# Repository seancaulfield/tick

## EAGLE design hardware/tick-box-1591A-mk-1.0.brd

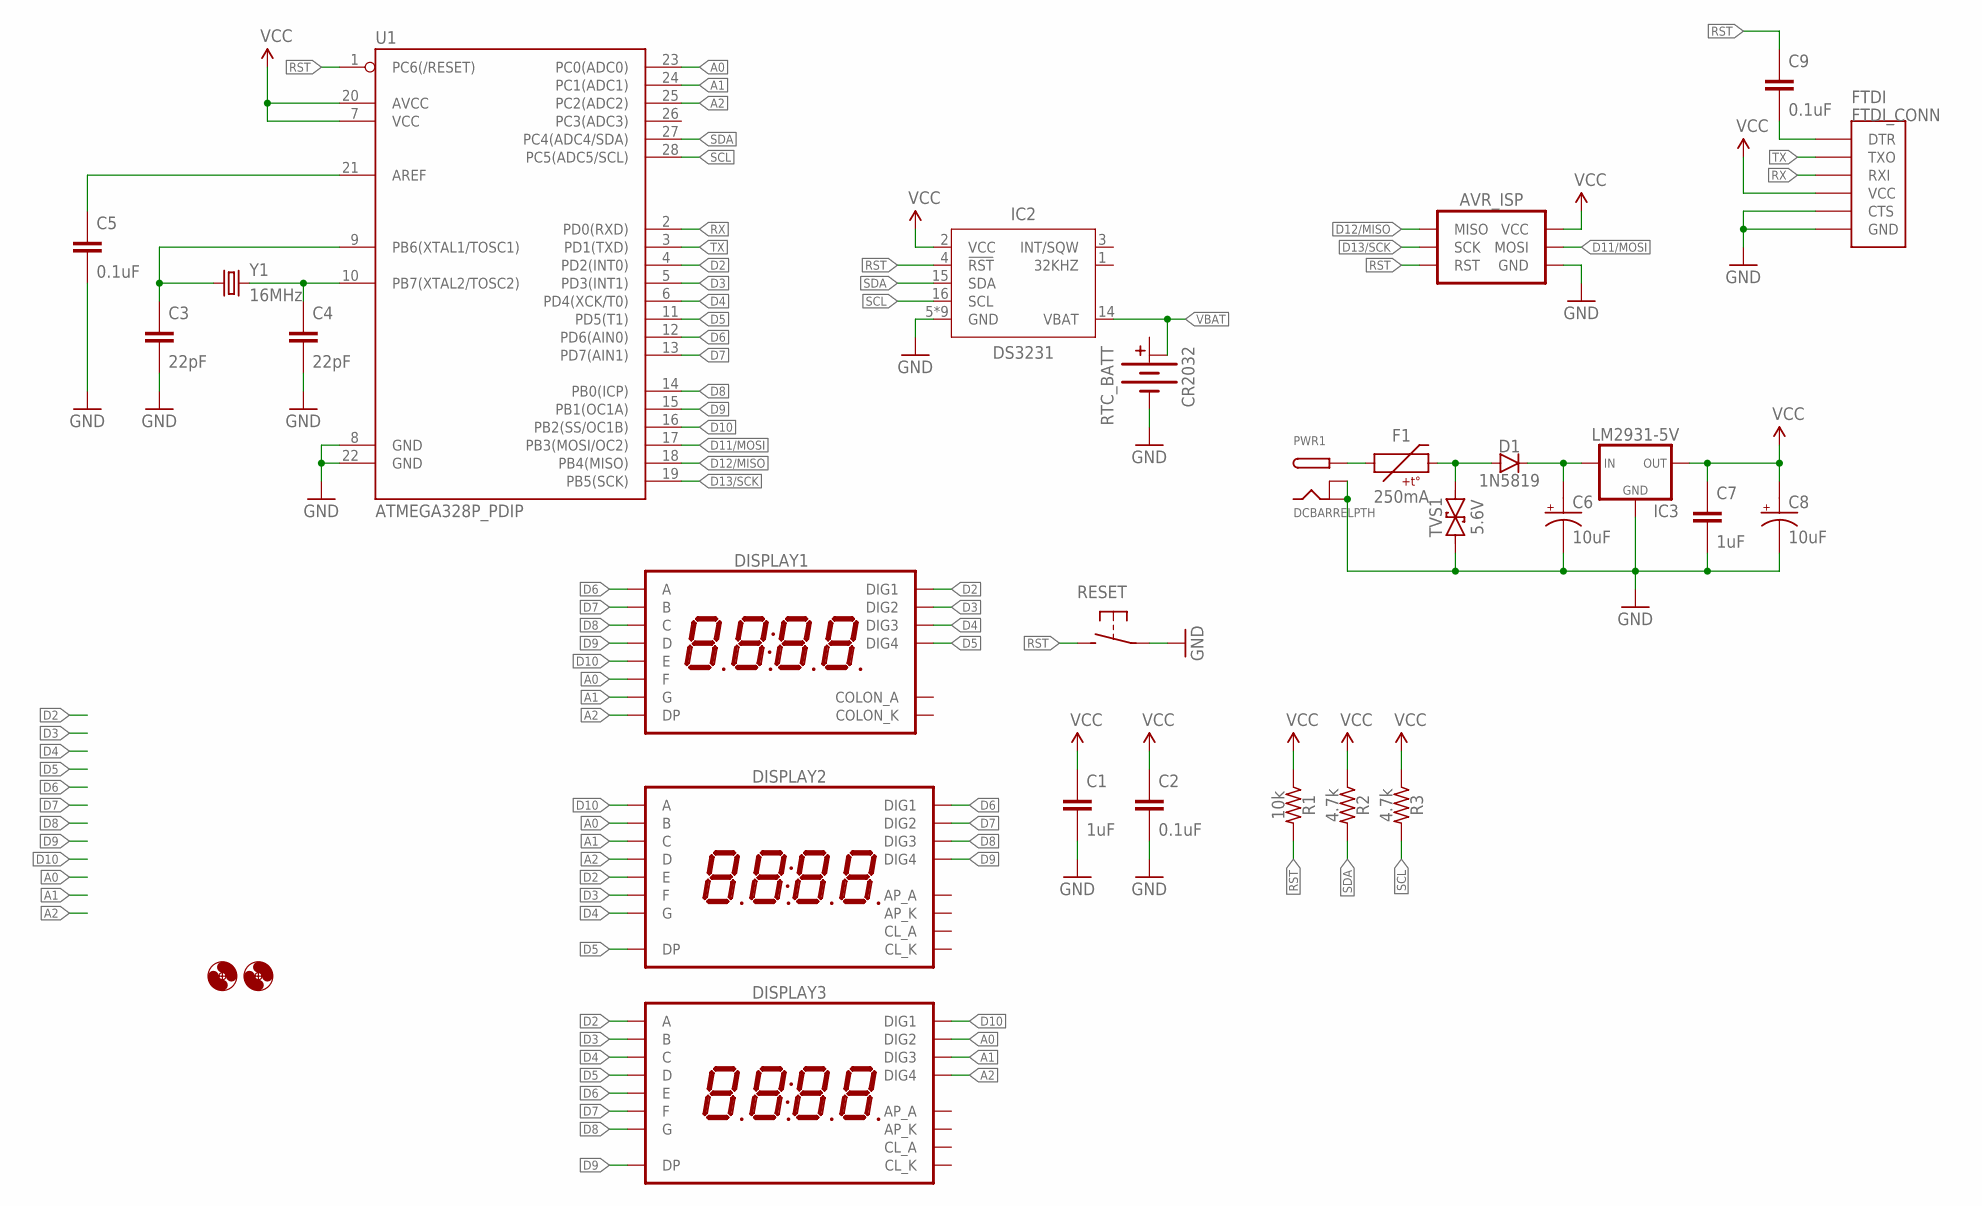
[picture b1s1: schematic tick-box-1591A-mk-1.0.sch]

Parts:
AVR_ISP: AVR_SPI_PRG_6PTH; 2X3
C1, C7: 1uF; C025-024X044
C2, C5, C9: 0.1uF; C025-024X044
C3, C4: 22pF; C025-024X044
C6, C8: 10uF; E2-5
D1: 1N5819; DIODE-10.16MM
DISPLAY1: 7SEG_4DIGIT_COLON14.2MM-CC-NS; 7SEG_4DIG_NS
DISPLAY2, DISPLAY3: 7SEG_4DIGIT_COLON_APOS; 7SEG_4DIG_10MM
F1: 250mA; PTC-PTH-5.08MM
FTDI: FTDI_CONN
H1, H2: HOLE#2; HOLE-#2
IC2: DS3231; SO16W
IC3: LM2931-5V; TO-92-AMMO
PWR1: DCBARRELPTH; DCJACK_2MM_PTH
R1: 10k; RESISTOR-AXIAL-PTH-7.62MM
R2, R3: 4.7k; RESISTOR-AXIAL-PTH-7.62MM
RESET: SPST-NO-TACT6MM-PTH-SMALL-PADS; DTS-6-SMALL-PADS
RTC_BATT: CR2032; BATTCON_20MM_MINE
TVS1: 5.6V; DO-41-TVS
U1: ATMEGA328P_PDIP; DIL28-3
Y1: 16MHz; HC49U-V

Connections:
A0: DISPLAY1.P$12 (F), DISPLAY2.16 (B), DISPLAY3.2 (DIG2), U1.23 (PC0(ADC0))
A1: DISPLAY1.P$5 (G), DISPLAY2.13 (C), DISPLAY3.6 (DIG3), U1.24 (PC1(ADC1))
A2: DISPLAY1.P$3 (DP), DISPLAY2.3 (D), DISPLAY3.8 (DIG4), U1.25 (PC2(ADC2))
D2: DISPLAY1.P$14 (DIG1), DISPLAY2.5 (E), DISPLAY3.14 (A), U1.4 (PD2(INT0))
D3: DISPLAY1.P$11 (DIG2), DISPLAY2.11 (F), DISPLAY3.16 (B), U1.5 (PD3(INT1))
D4: DISPLAY1.P$10 (DIG3), DISPLAY2.15 (G), DISPLAY3.13 (C), U1.6 (PD4(XCK/T0))
D5: DISPLAY1.P$6 (DIG4), DISPLAY2.7 (DP), DISPLAY3.3 (D), U1.11 (PD5(T1))
D6: DISPLAY1.P$13 (A), DISPLAY2.1 (DIG1), DISPLAY3.5 (E), U1.12 (PD6(AIN0))
D7: DISPLAY1.P$9 (B), DISPLAY2.2 (DIG2), DISPLAY3.11 (F), U1.13 (PD7(AIN1))
D8: DISPLAY1.P$4 (C), DISPLAY2.6 (DIG3), DISPLAY3.15 (G), U1.14 (PB0(ICP))
D9: DISPLAY1.P$2 (D), DISPLAY2.8 (DIG4), DISPLAY3.7 (DP), U1.15 (PB1(OC1A))
D10: DISPLAY1.P$1 (E), DISPLAY2.14 (A), DISPLAY3.1 (DIG1), U1.16 (PB2(SS/OC1B))
D11/MOSI: AVR_ISP.4 (MOSI), U1.17 (PB3(MOSI/OC2))
D12/MISO: AVR_ISP.1 (MISO), U1.18 (PB4(MISO))
D13/SCK: AVR_ISP.3 (SCK), U1.19 (PB5(SCK))
GND: AVR_ISP.6 (GND), C1.2, C2.2, C3.2, C4.2, C5.2, C6.-, C7.2, C8.-, FTDI.CTS, FTDI.GND, IC2.5 (GND), IC2.6 (GND), IC2.7 (GND), IC2.8 (GND), IC2.9 (GND), IC2.10 (GND), IC2.11 (GND), IC2.12 (GND), IC2.13 (GND), IC3.2 (GND), PWR1.BRK, PWR1.GND, RESET.1, RESET.2 (1), RTC_BATT.BOTTOM (-), TVS1.P$1 (1), U1.8 (GND), U1.22 (GND)
unnamed: C4.1, U1.10 (PB7(XTAL2/TOSC2)), Y1.2
unnamed: C3.1, U1.9 (PB6(XTAL1/TOSC1)), Y1.1
unnamed: C6.+, D1.C, IC3.1 (IN)
unnamed: F1.P$1 (1), PWR1.PWR
unnamed: C5.1, U1.21 (AREF)
unnamed: D1.A, F1.P$2 (2), TVS1.P$2 (2)
unnamed: C9.2, FTDI.DTR
RST: AVR_ISP.5 (RST), C9.1, IC2.4 (!RST), R1.P$2 (2), RESET.3 (2), RESET.4 (2), U1.1 (PC6(/RESET))
RX: FTDI.RXI, U1.2 (PD0(RXD))
SCL: IC2.16 (SCL), R3.P$2 (2), U1.28 (PC5(ADC5/SCL))
SDA: IC2.15 (SDA), R2.P$2 (2), U1.27 (PC4(ADC4/SDA))
TX: FTDI.TXO, U1.3 (PD1(TXD))
VBAT: IC2.14 (VBAT), RTC_BATT.TOP@2 (+1)
VCC: AVR_ISP.2 (VCC), C1.1, C2.1, C7.1, C8.+, FTDI.VCC, IC2.2 (VCC), IC3.3 (OUT), R1.P$1 (1), R2.P$1 (1), R3.P$1 (1), U1.7 (VCC), U1.20 (AVCC)

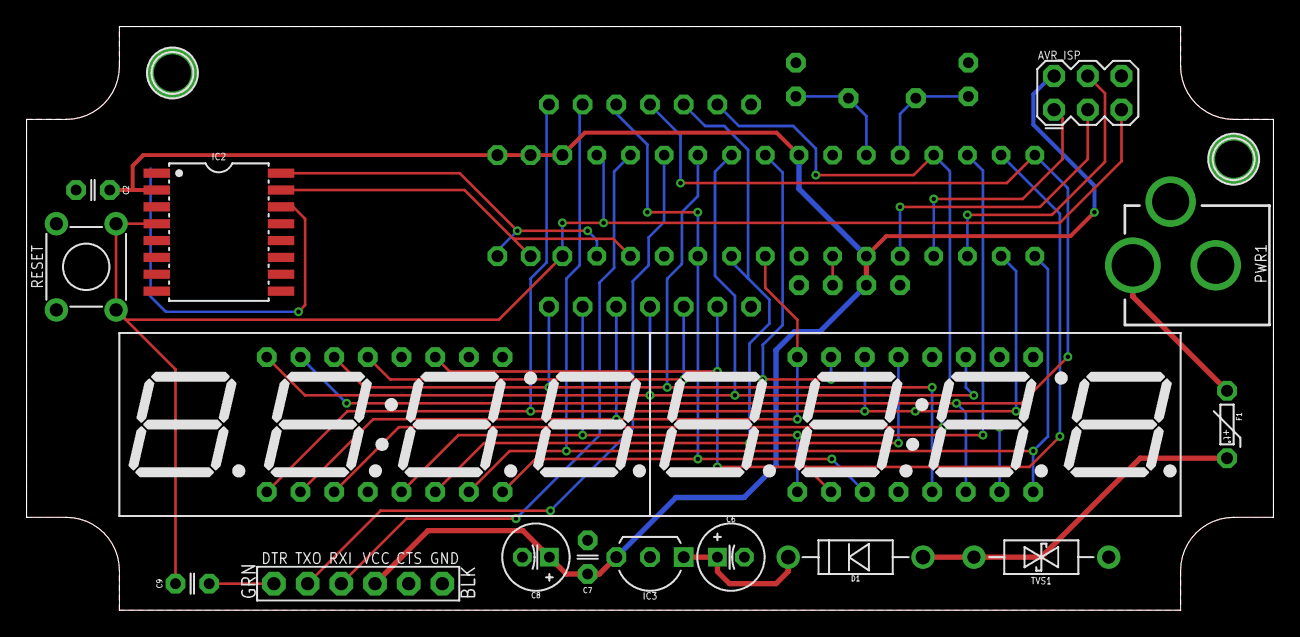
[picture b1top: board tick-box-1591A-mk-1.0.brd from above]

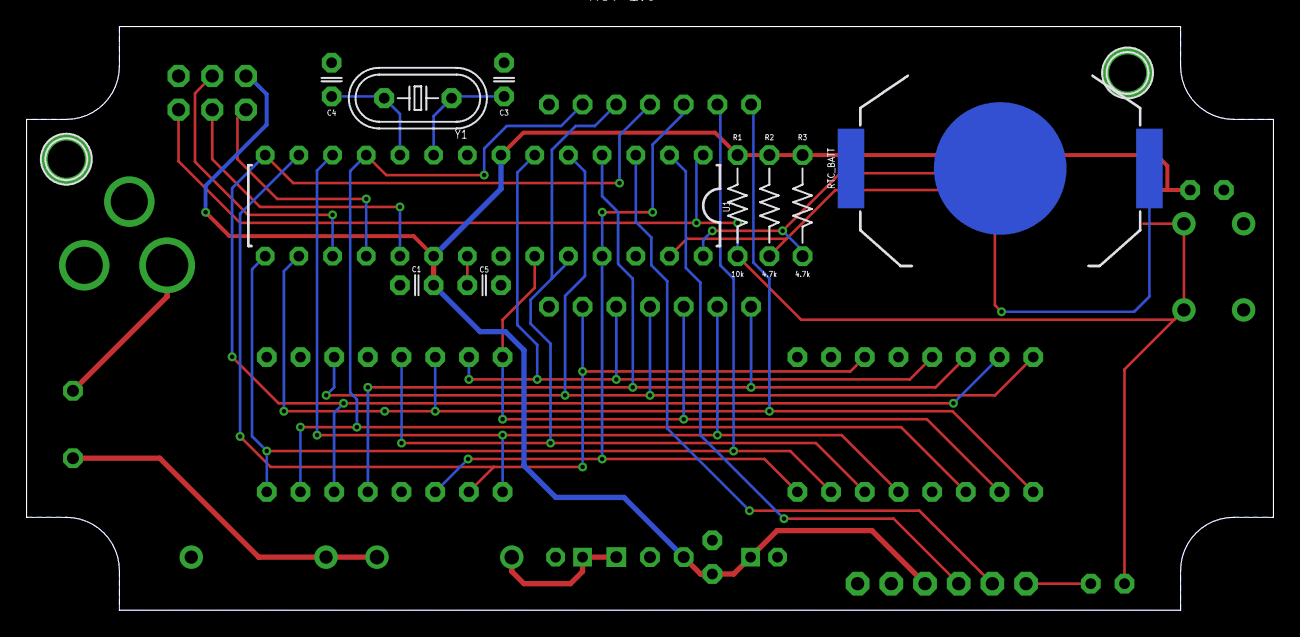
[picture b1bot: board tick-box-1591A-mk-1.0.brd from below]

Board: 2 copper layers, 94.0 x 44.0 mm, 29 parts (10 on the bottom side), 30 nets.

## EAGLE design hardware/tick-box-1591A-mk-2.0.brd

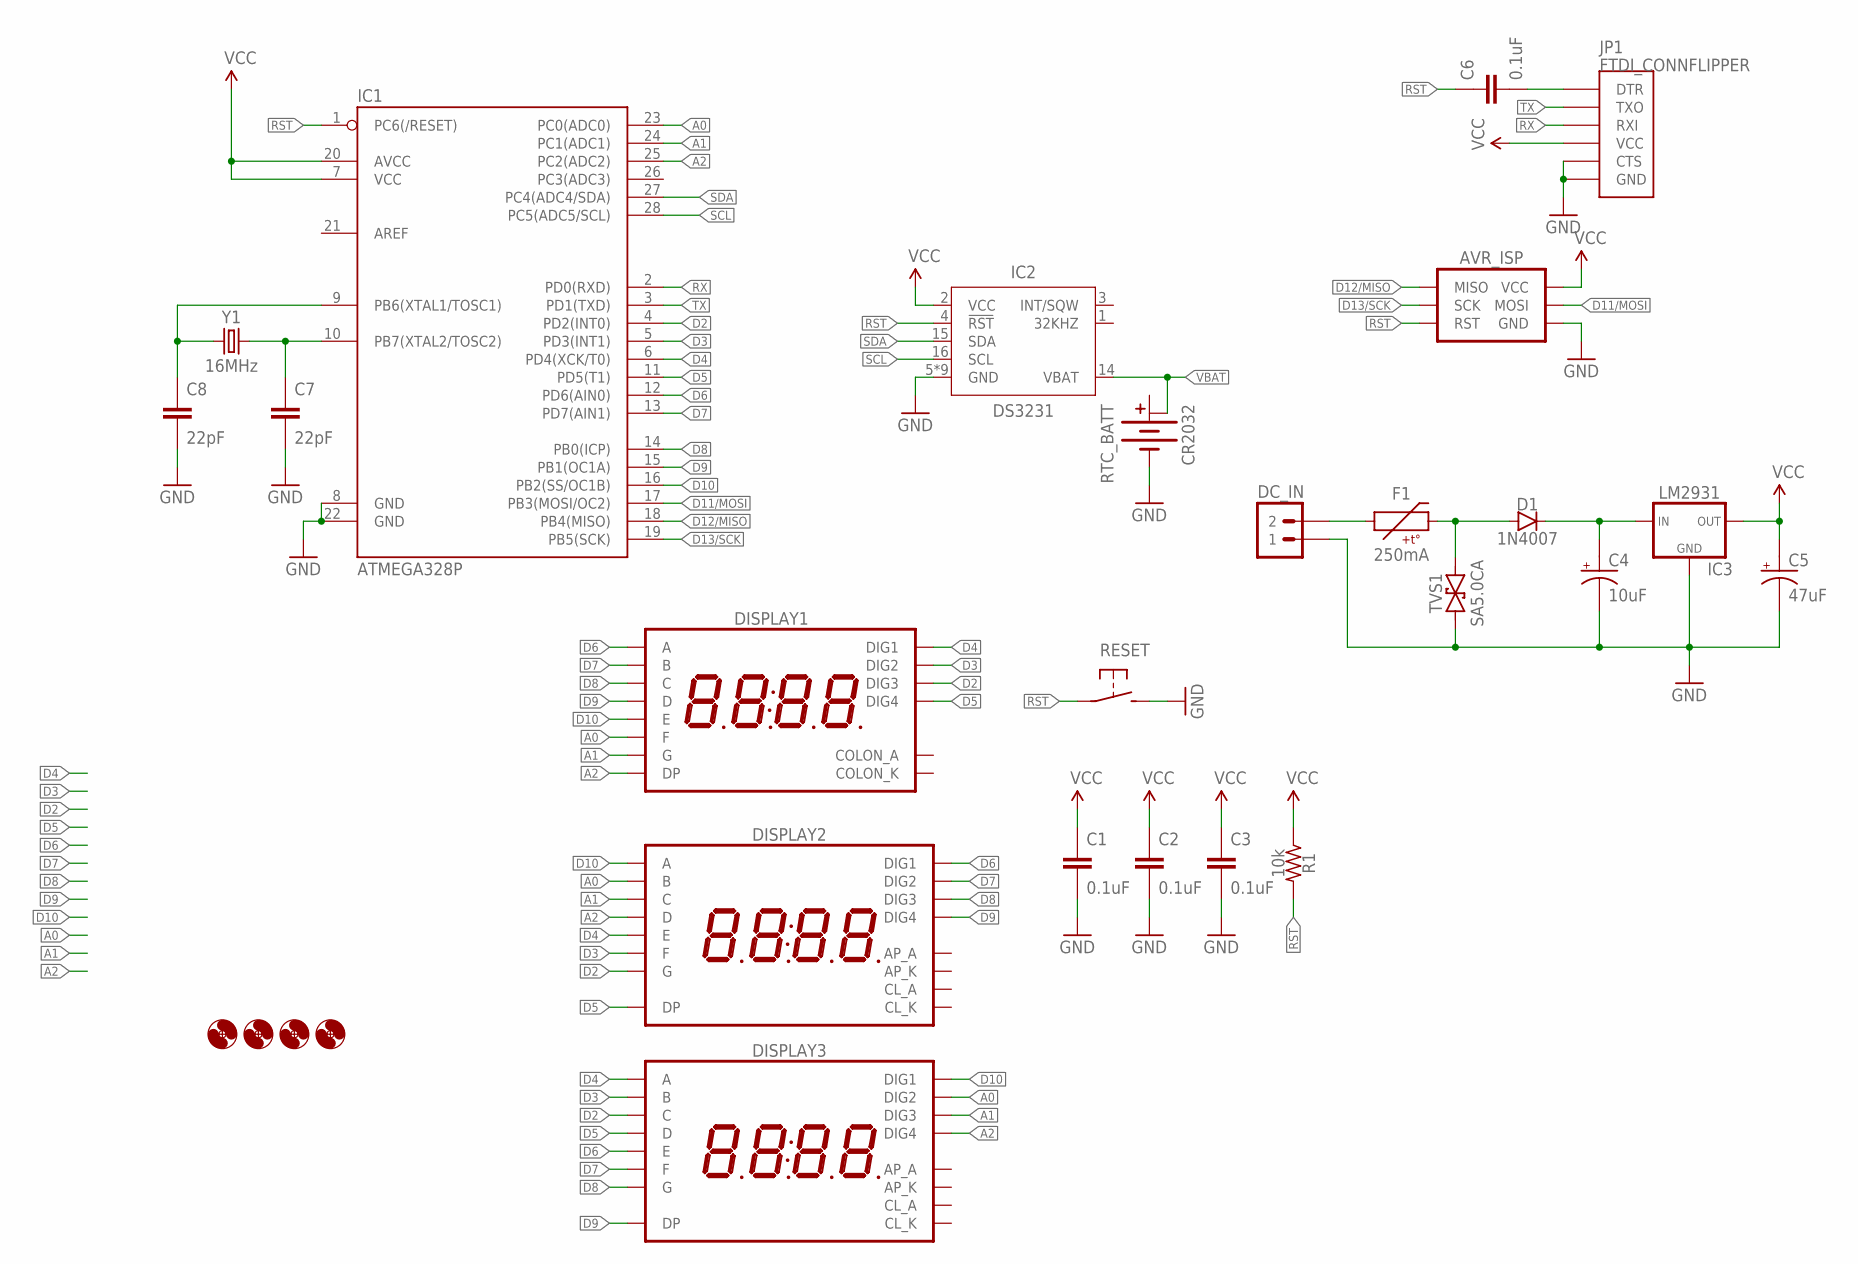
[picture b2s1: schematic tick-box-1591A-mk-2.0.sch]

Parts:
AVR_ISP: AVR_SPI_PRG_6PTH; 2X3
C1, C2, C3, C6: 0.1uF; C025-024X044
C4: 10uF; E2-4
C5: 47uF; E2-4
C7, C8: 22pF; C025-024X044
D1: 1N4007; DIODE-10.16MM
DC_IN: M02PTH; 1X02
DISPLAY1: 7SEG_4DIGIT_COLON14.2MM-CC-NS; 7SEG_4DIG_NS
DISPLAY2, DISPLAY3: 7SEG_4DIGIT_COLON_APOS; 7SEG_4DIG_10MM
F1: 250mA; PTC-1206
H1, H2, H3, H4: HOLE#2; HOLE-#2
IC1: ATMEGA328P; DIL28-3
IC2: DS3231; SO16W
IC3: LM2931; TO-92-AMMO
JP1: FTDI_CONNFLIPPER; FTDI_CONN_FLIP
R1: 10k; RESISTOR-AXIAL-PTH-6.35MM
RESET: SPST-NO-TACT3MM-PTH-SMALL-PADS; DTS-3-SMALL-PADS
RTC_BATT: CR2032; BATTCON_20MM_MINE
TVS1: SA5.0CA; DO-41-TVS-BI-10.16MM
Y1: 16MHz; HC49U-V

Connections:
A0: DISPLAY1.P$12 (F), DISPLAY2.16 (B), DISPLAY3.2 (DIG2), IC1.23 (PC0(ADC0))
A1: DISPLAY1.P$5 (G), DISPLAY2.13 (C), DISPLAY3.6 (DIG3), IC1.24 (PC1(ADC1))
A2: DISPLAY1.P$3 (DP), DISPLAY2.3 (D), DISPLAY3.8 (DIG4), IC1.25 (PC2(ADC2))
D2: DISPLAY1.P$10 (DIG3), DISPLAY2.15 (G), DISPLAY3.13 (C), IC1.4 (PD2(INT0))
D3: DISPLAY1.P$11 (DIG2), DISPLAY2.11 (F), DISPLAY3.16 (B), IC1.5 (PD3(INT1))
D4: DISPLAY1.P$14 (DIG1), DISPLAY2.5 (E), DISPLAY3.14 (A), IC1.6 (PD4(XCK/T0))
D5: DISPLAY1.P$6 (DIG4), DISPLAY2.7 (DP), DISPLAY3.3 (D), IC1.11 (PD5(T1))
D6: DISPLAY1.P$13 (A), DISPLAY2.1 (DIG1), DISPLAY3.5 (E), IC1.12 (PD6(AIN0))
D7: DISPLAY1.P$9 (B), DISPLAY2.2 (DIG2), DISPLAY3.11 (F), IC1.13 (PD7(AIN1))
D8: DISPLAY1.P$4 (C), DISPLAY2.6 (DIG3), DISPLAY3.15 (G), IC1.14 (PB0(ICP))
D9: DISPLAY1.P$2 (D), DISPLAY2.8 (DIG4), DISPLAY3.7 (DP), IC1.15 (PB1(OC1A))
D10: DISPLAY1.P$1 (E), DISPLAY2.14 (A), DISPLAY3.1 (DIG1), IC1.16 (PB2(SS/OC1B))
D11/MOSI: AVR_ISP.4 (MOSI), IC1.17 (PB3(MOSI/OC2))
D12/MISO: AVR_ISP.1 (MISO), IC1.18 (PB4(MISO))
D13/SCK: AVR_ISP.3 (SCK), IC1.19 (PB5(SCK))
GND: AVR_ISP.6 (GND), C1.2, C2.2, C3.2, C4.-, C5.-, C7.2, C8.2, DC_IN.1, IC1.8 (GND), IC1.22 (GND), IC2.5 (GND), IC2.6 (GND), IC2.7 (GND), IC2.8 (GND), IC2.9 (GND), IC2.10 (GND), IC2.11 (GND), IC2.12 (GND), IC2.13 (GND), IC3.2 (GND), JP1.CTS, JP1.GND, RESET.2, RTC_BATT.BOTTOM (-), TVS1.P$1 (1)
unnamed: C7.1, IC1.10 (PB7(XTAL2/TOSC2)), Y1.1
unnamed: C8.1, IC1.9 (PB6(XTAL1/TOSC1)), Y1.2
unnamed: D1.A, F1.2, TVS1.P$2 (2)
unnamed: DC_IN.2, F1.1
unnamed: C4.+, D1.C, IC3.1 (IN)
unnamed: C6.2, JP1.DTR
RST: AVR_ISP.5 (RST), C6.1, IC1.1 (PC6(/RESET)), IC2.4 (!RST), R1.P$2 (2), RESET.1
RX: IC1.2 (PD0(RXD)), JP1.RXI
SCL: IC1.28 (PC5(ADC5/SCL)), IC2.16 (SCL)
SDA: IC1.27 (PC4(ADC4/SDA)), IC2.15 (SDA)
TX: IC1.3 (PD1(TXD)), JP1.TXO
VBAT: IC2.14 (VBAT), RTC_BATT.TOP@2 (+1)
VCC: AVR_ISP.2 (VCC), C1.1, C2.1, C3.1, C5.+, IC1.7 (VCC), IC1.20 (AVCC), IC2.2 (VCC), IC3.3 (OUT), JP1.VCC, R1.P$1 (1)

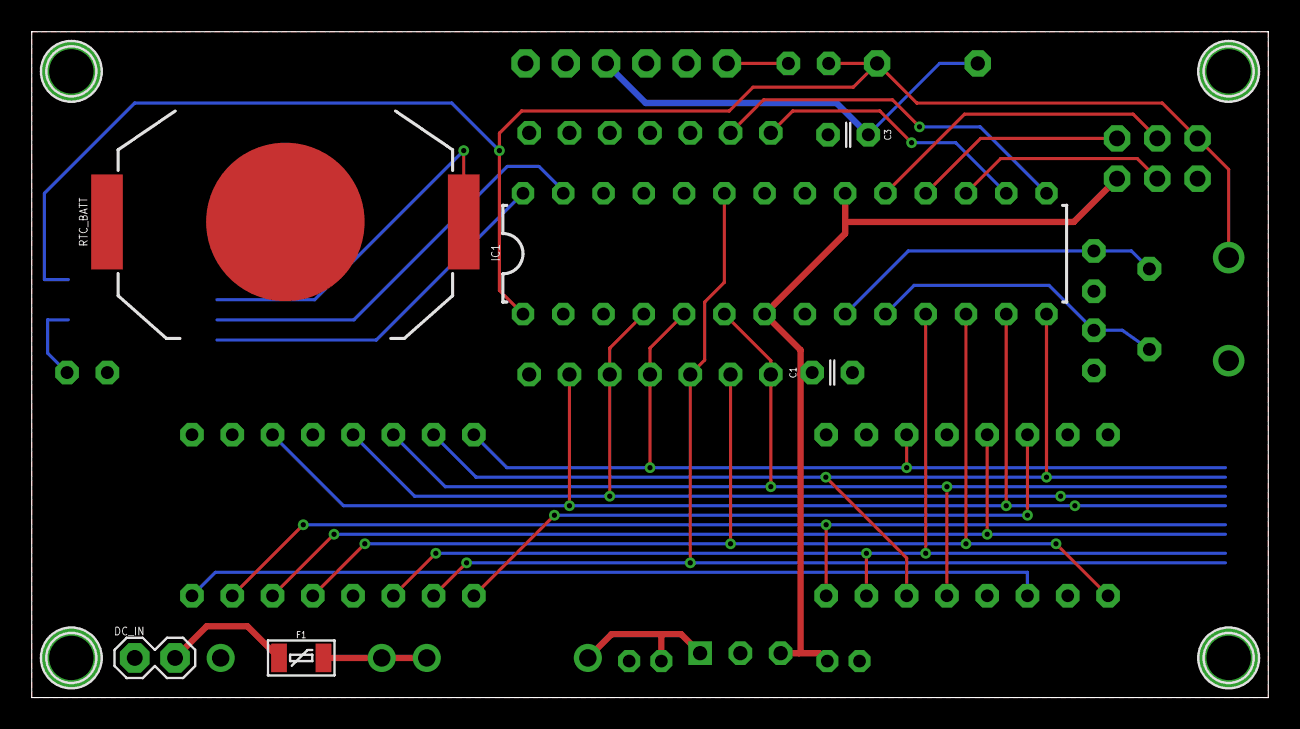
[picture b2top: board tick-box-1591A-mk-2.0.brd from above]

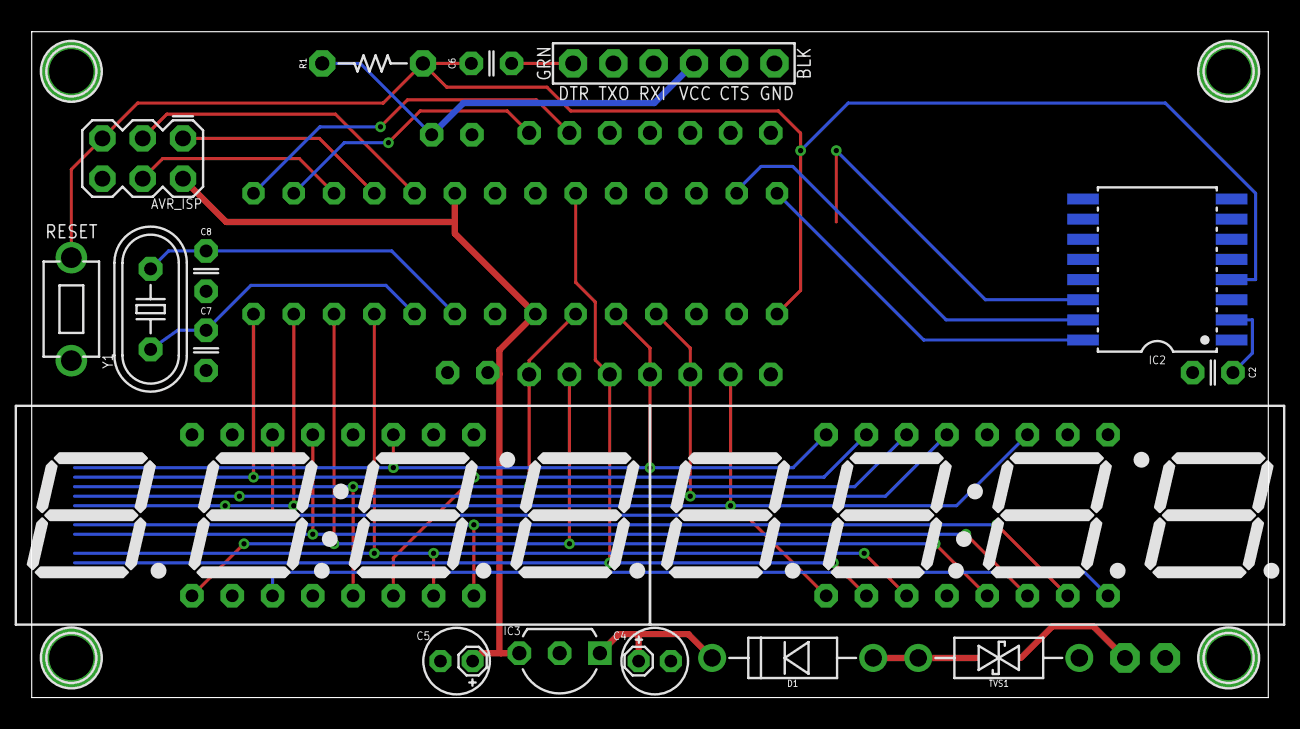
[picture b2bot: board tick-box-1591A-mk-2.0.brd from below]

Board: 2 copper layers, 78.0 x 42.0 mm, 28 parts (18 on the bottom side), 29 nets.

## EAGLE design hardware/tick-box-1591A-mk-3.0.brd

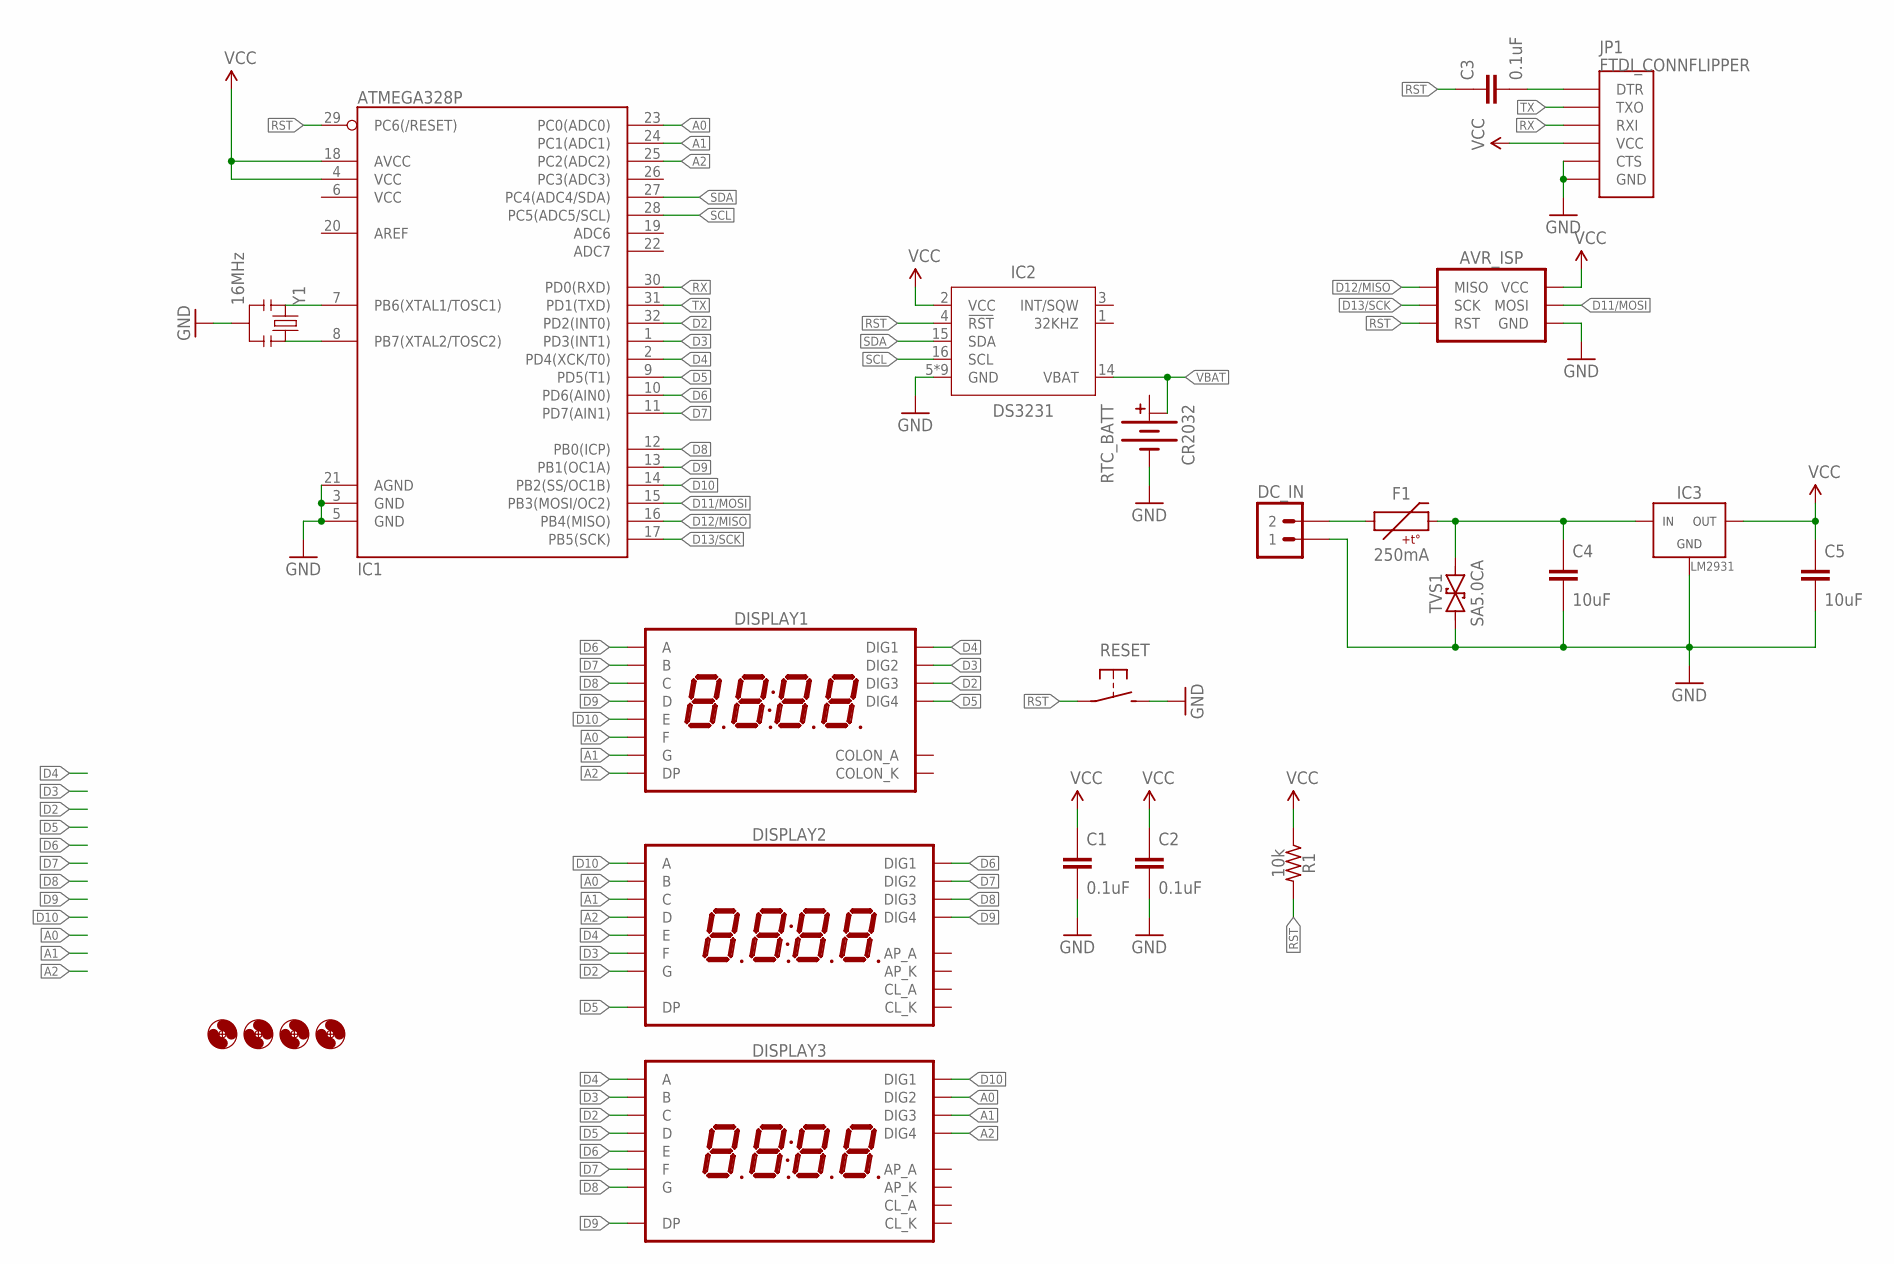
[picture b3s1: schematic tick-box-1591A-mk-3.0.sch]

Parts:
AVR_ISP: AVR_SPI_PRG_6PTH; 2X3
C1, C2, C3: 0.1uF; C0603
C4, C5: 10uF; C1206
DC_IN: M02PTH; 1X02
DISPLAY1: 7SEG_4DIGIT_COLON14.2MM-CC-NS; 7SEG_4DIG_NS
DISPLAY2, DISPLAY3: 7SEG_4DIGIT_COLON_APOS; 7SEG_4DIG_10MM
F1: 250mA; PTC-1206
H1, H2, H3, H4: HOLE#2; HOLE-#2
IC1: ATMEGA328P; TQFP32-08
IC2: DS3231; SO16W
IC3: LM2931; SO08
JP1: FTDI_CONNFLIPPER; FTDI_CONN_FLIP
R1: 10k; R0603
RESET: SPST-NO-TACT3MM-PTH-SMALL-PADS; DTS-3-SMALL-PADS
RTC_BATT: CR2032; BATTCON_20MM_MINE
TVS1: SA5.0CA; SMA-DIODE-TVS-BIDIR
Y1: 16MHz; CSTCE_V_RESONATOR

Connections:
A0: DISPLAY1.P$12 (F), DISPLAY2.16 (B), DISPLAY3.2 (DIG2), IC1.23 (PC0(ADC0))
A1: DISPLAY1.P$5 (G), DISPLAY2.13 (C), DISPLAY3.6 (DIG3), IC1.24 (PC1(ADC1))
A2: DISPLAY1.P$3 (DP), DISPLAY2.3 (D), DISPLAY3.8 (DIG4), IC1.25 (PC2(ADC2))
D2: DISPLAY1.P$10 (DIG3), DISPLAY2.15 (G), DISPLAY3.13 (C), IC1.32 (PD2(INT0))
D3: DISPLAY1.P$11 (DIG2), DISPLAY2.11 (F), DISPLAY3.16 (B), IC1.1 (PD3(INT1))
D4: DISPLAY1.P$14 (DIG1), DISPLAY2.5 (E), DISPLAY3.14 (A), IC1.2 (PD4(XCK/T0))
D5: DISPLAY1.P$6 (DIG4), DISPLAY2.7 (DP), DISPLAY3.3 (D), IC1.9 (PD5(T1))
D6: DISPLAY1.P$13 (A), DISPLAY2.1 (DIG1), DISPLAY3.5 (E), IC1.10 (PD6(AIN0))
D7: DISPLAY1.P$9 (B), DISPLAY2.2 (DIG2), DISPLAY3.11 (F), IC1.11 (PD7(AIN1))
D8: DISPLAY1.P$4 (C), DISPLAY2.6 (DIG3), DISPLAY3.15 (G), IC1.12 (PB0(ICP))
D9: DISPLAY1.P$2 (D), DISPLAY2.8 (DIG4), DISPLAY3.7 (DP), IC1.13 (PB1(OC1A))
D10: DISPLAY1.P$1 (E), DISPLAY2.14 (A), DISPLAY3.1 (DIG1), IC1.14 (PB2(SS/OC1B))
D11/MOSI: AVR_ISP.4 (MOSI), IC1.15 (PB3(MOSI/OC2))
D12/MISO: AVR_ISP.1 (MISO), IC1.16 (PB4(MISO))
D13/SCK: AVR_ISP.3 (SCK), IC1.17 (PB5(SCK))
GND: AVR_ISP.6 (GND), C1.2, C2.2, C4.2, C5.2, DC_IN.1, IC1.3 (GND), IC1.5 (GND), IC1.21 (AGND), IC2.5 (GND), IC2.6 (GND), IC2.7 (GND), IC2.8 (GND), IC2.9 (GND), IC2.10 (GND), IC2.11 (GND), IC2.12 (GND), IC2.13 (GND), IC3.2 (GND), IC3.3 (GND), IC3.4 (GND), IC3.5 (GND), IC3.6 (GND), IC3.7 (GND), JP1.CTS, JP1.GND, RESET.2, RTC_BATT.BOTTOM (-), TVS1.1, Y1.2
unnamed: IC1.7 (PB6(XTAL1/TOSC1)), Y1.3
unnamed: IC1.8 (PB7(XTAL2/TOSC2)), Y1.1
unnamed: DC_IN.2, F1.1
unnamed: C4.1, F1.2, IC3.8 (IN), TVS1.2
unnamed: C3.2, JP1.DTR
RST: AVR_ISP.5 (RST), C3.1, IC1.29 (PC6(/RESET)), IC2.4 (!RST), R1.2, RESET.1
RX: IC1.30 (PD0(RXD)), JP1.RXI
SCL: IC1.28 (PC5(ADC5/SCL)), IC2.16 (SCL)
SDA: IC1.27 (PC4(ADC4/SDA)), IC2.15 (SDA)
TX: IC1.31 (PD1(TXD)), JP1.TXO
VBAT: IC2.14 (VBAT), RTC_BATT.TOP@2 (+1)
VCC: AVR_ISP.2 (VCC), C1.1, C2.1, C5.1, IC1.4 (VCC), IC1.18 (AVCC), IC2.2 (VCC), IC3.1 (OUT), JP1.VCC, R1.1

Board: 2 copper layers, 24 parts (8 on the bottom side), 28 nets, no tracks yet.

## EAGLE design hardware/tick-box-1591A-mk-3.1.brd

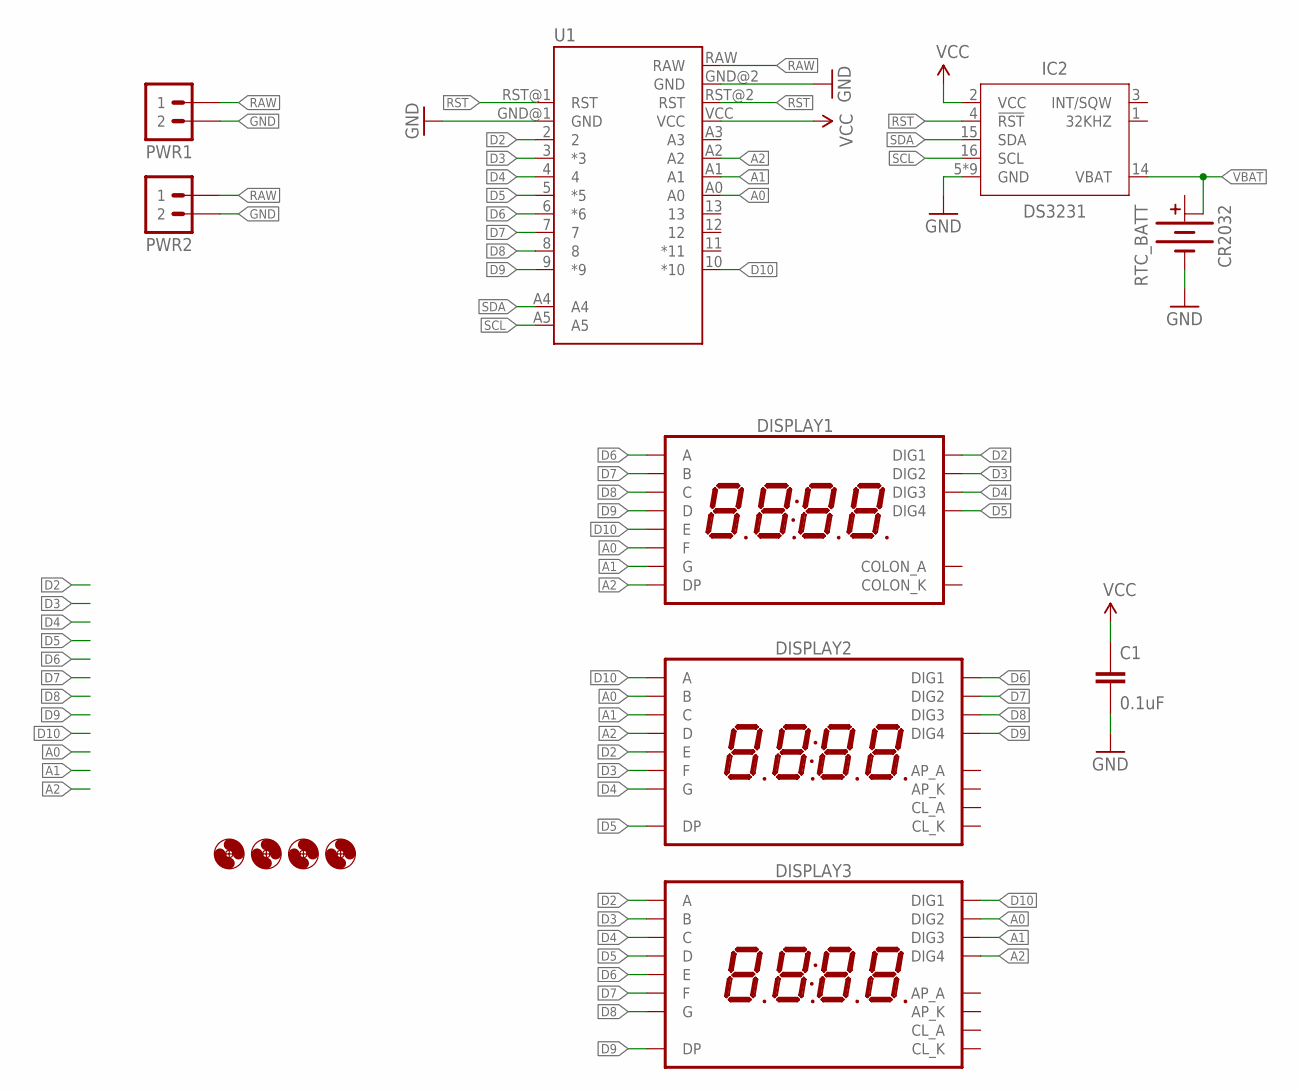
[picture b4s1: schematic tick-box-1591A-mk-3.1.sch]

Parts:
C1: 0.1uF; C025-024X044
DISPLAY1: 7SEG_4DIGIT_COLON14.2MM-CC-NS; 7SEG_4DIG_NS
DISPLAY2, DISPLAY3: 7SEG_4DIGIT_COLON_APOS; 7SEG_4DIG_10MM
H1, H2, H3, H4: HOLE#2; HOLE-#2
IC2: DS3231; SO16W
PWR1, PWR2: M02PTH-CENTERED; 1X02-CENTER
RTC_BATT: CR2032; BATTCON_20MM_MINE
U1: ARDUINO_PRO_MINI_TICK

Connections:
A0: DISPLAY1.P$12 (F), DISPLAY2.16 (B), DISPLAY3.2 (DIG2), U1.A0
A1: DISPLAY1.P$5 (G), DISPLAY2.13 (C), DISPLAY3.6 (DIG3), U1.A1
A2: DISPLAY1.P$3 (DP), DISPLAY2.3 (D), DISPLAY3.8 (DIG4), U1.A2
D2: DISPLAY1.P$14 (DIG1), DISPLAY2.5 (E), DISPLAY3.14 (A), U1.2
D3: DISPLAY1.P$11 (DIG2), DISPLAY2.11 (F), DISPLAY3.16 (B), U1.3 (*3)
D4: DISPLAY1.P$10 (DIG3), DISPLAY2.15 (G), DISPLAY3.13 (C), U1.4
D5: DISPLAY1.P$6 (DIG4), DISPLAY2.7 (DP), DISPLAY3.3 (D), U1.5 (*5)
D6: DISPLAY1.P$13 (A), DISPLAY2.1 (DIG1), DISPLAY3.5 (E), U1.6 (*6)
D7: DISPLAY1.P$9 (B), DISPLAY2.2 (DIG2), DISPLAY3.11 (F), U1.7
D8: DISPLAY1.P$4 (C), DISPLAY2.6 (DIG3), DISPLAY3.15 (G), U1.8
D9: DISPLAY1.P$2 (D), DISPLAY2.8 (DIG4), DISPLAY3.7 (DP), U1.9 (*9)
D10: DISPLAY1.P$1 (E), DISPLAY2.14 (A), DISPLAY3.1 (DIG1), U1.10 (*10)
GND: C1.2, IC2.5 (GND), IC2.6 (GND), IC2.7 (GND), IC2.8 (GND), IC2.9 (GND), IC2.10 (GND), IC2.11 (GND), IC2.12 (GND), IC2.13 (GND), PWR1.2, PWR2.2, RTC_BATT.BOTTOM (-), U1.GND@1 (GND), U1.GND@2 (GND)
RAW: PWR1.1, PWR2.1, U1.RAW
RST: IC2.4 (!RST), U1.RST@1 (RST), U1.RST@2 (RST)
SCL: IC2.16 (SCL), U1.A5
SDA: IC2.15 (SDA), U1.A4
VBAT: IC2.14 (VBAT), RTC_BATT.TOP@2 (+1)
VCC: C1.1, IC2.2 (VCC), U1.VCC

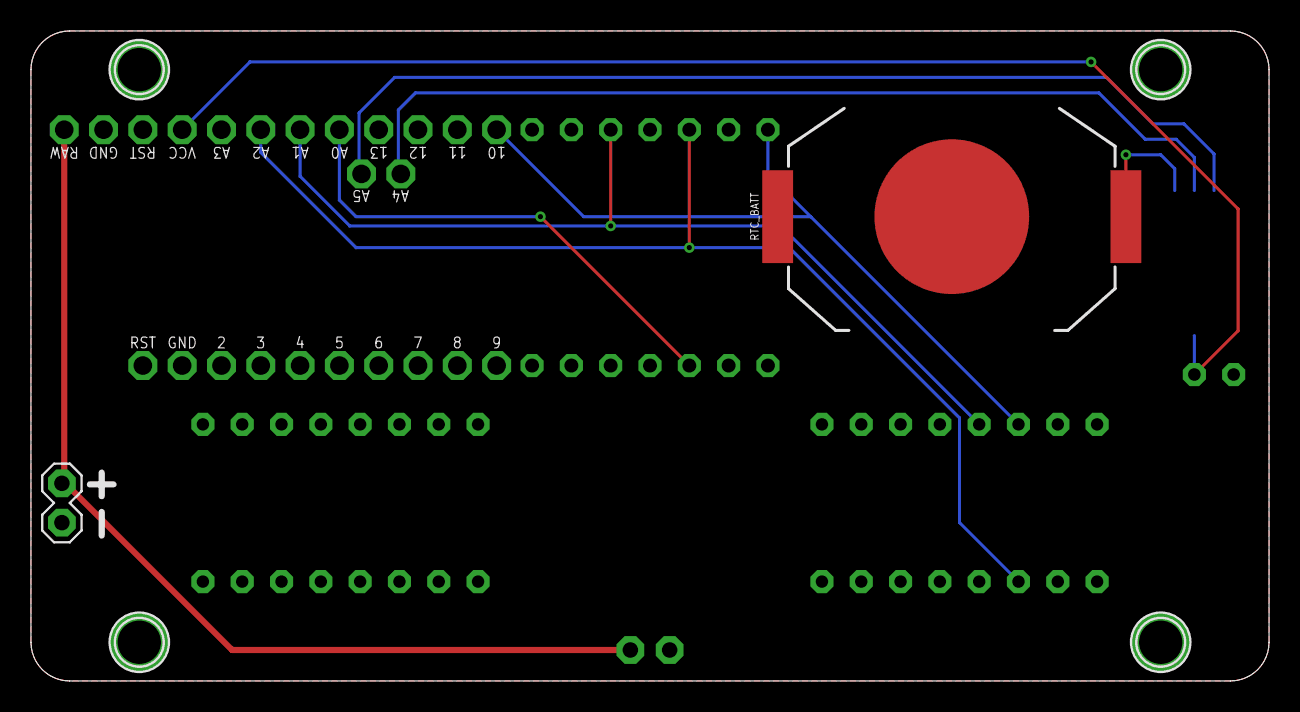
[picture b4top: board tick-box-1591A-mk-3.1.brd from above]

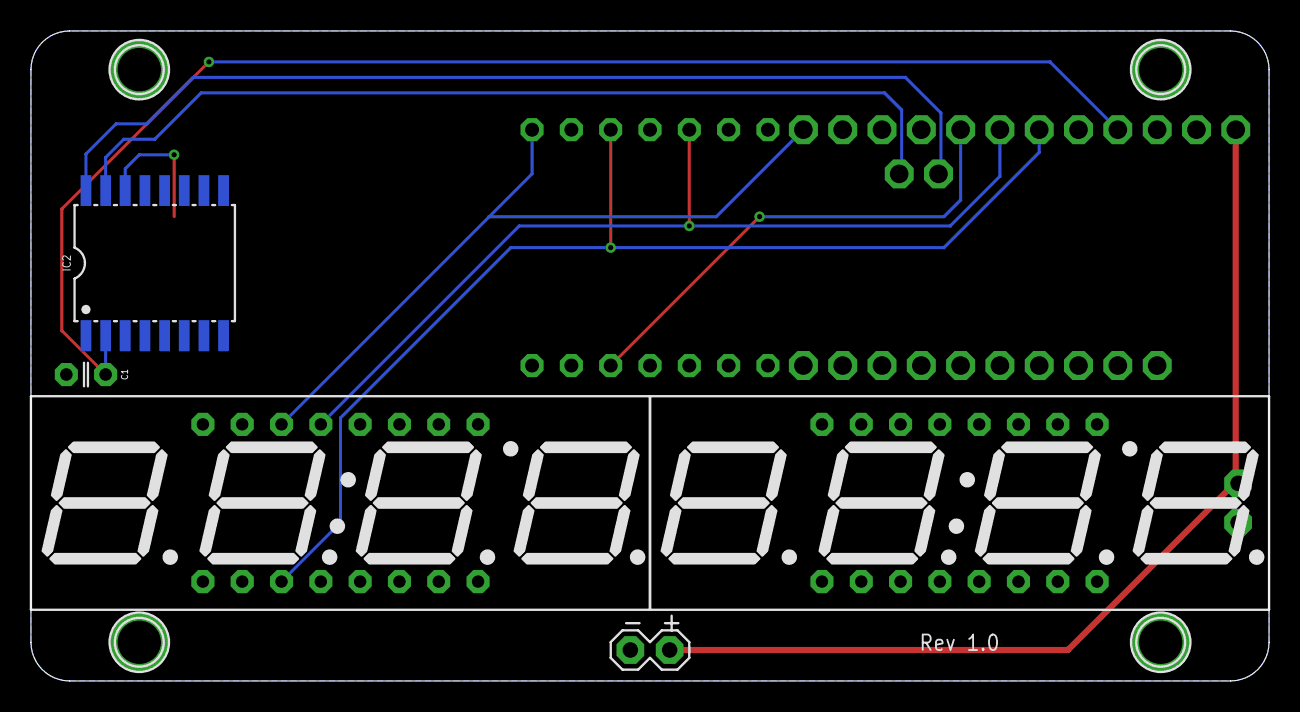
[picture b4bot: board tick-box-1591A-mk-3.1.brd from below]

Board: 2 copper layers, 80.0 x 42.0 mm, 13 parts (6 on the bottom side), 19 nets.

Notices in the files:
parts and their libraries:
A_butts: Released under the Creative Commons Attribution Share-Alike 4.0 License
A_butts: https://creativecommons.org/licenses/by-sa/4.0
A_butts: Released under the Creative Commons
